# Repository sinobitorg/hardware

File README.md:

# sino:bit 八卦单机板

A single-board microcontroller for computer education in China<br>
专为中国电脑教育打造的一款微型单机板

The sino:bit is the first Chinese OSHWA Certified project:<br>
这块单机板是第一块中国真正被开源协会认证的项目<br>

### Quick Start
[Elecrow sells the sino:bit here.](https://www.elecrow.com/sino-bit-v1-0.html)

Adafruit has an [excellent tutorial written by David Astels](https://learn.adafruit.com/sino-bit-with-arduino/dastels-overview)

If you want to make an enclosure, [you can download CAD files of the board here.](https://a360.co/2mymH0g)

## Contents 内容
- [Introduction 介绍](#introduction-介绍)
  - [What it is 它是什么](#what-it-is-它是什么)
  - [Why it was created 创造原因](#why-it-was-created-创造原因)
  - [What it means 八卦单机板的意义](#what-it-means-八卦单机板的意义)
  - [Who are we 我们是谁](#who-are-we-我们是谁)
- [License 许可协议](#license-许可协议)

## Introduction 介绍

### What it is 它是什么

The sino:bit a single-board microcontroller designed for computer education in China. It is based on the [Calliope mini](https://calliope.cc) with permission of the [Calliope mini project](https://github.com/calliope-mini/).

While several modifications are planned, the first was to upgrade the LED matrix from 5x5 to 12x12. This allows for support of Chinese, Japanese, Hindi, Arabic and other non-Latin character based languages. Without this, the vast majority of the World's children cannot experience the thrill of that first "Hello World" in their own language.

八卦单机板是为中国打造的一款微型可编程计算机。是基于德国的 [Calliope mini](https://calliope.cc)获得官方准许后衍生出来的项目。在构思中国版本的时候有几个想法，其中一点就是把原有的5X5LED矩阵改为12X12。这样可支持多国语言，不仅只是英语，也可以显示中文，日本，印度语，阿拉伯语和其他不以拉丁语为基础的语言。如果保留原有的只是5X5矩阵，其他国家的孩子就无法体验到第一次显示屏弹出他们自己语言的“Hello, World”的那种激动兴奋的心情。

### Why it was created 创造原因

China has two issues to deal with in computer education. The first is the same as everyplace else in the world- the process of teaching coding and hardware fundamentals. The second is somewhat more unique to China and it's a problem we are known around the World for. How we copy. Children need to learn when we can copy, how we copy, and what our obligations are when we copy. Not out of any abstract moral obligation- but because copying and poor habits related to IP is standing in the way of China progressing economically.

If the quality and creativity of our engineering is going to improve, we need to begin teaching Open Source citizenship at a younger age. We cannot wait until engineers are graduating college to introduce them to the values of Open Source, by then habits are set and we have seen they are nearly impossible to change. This is a lesson that needs to be taught alongside other computing fundamentals from the time students are in primary school.

Our goal is that the sino:bit lineage- what it is derived from, what that means, and why Open Source is valuable; be taught from the beginning before a student writes their first line of code.

Original BBC micro:bits, in addition to not supporting Chinese language display, cannot compete on cost with locally made, license violating clones. Using these clones sets the worse possible example.

What China needs is an Open Source board priced appropriately for our level of economic development- cost-effective enough to supply one to every child as part of a nationally standardized curriculum, that is fully compliant with Open Source licenses and community standards.

在中国进行电脑教育面临着两大主要问题。第一个跟全世界一样的问题-利用更好的方法和途径去教育编程和硬件基础知识。第二个是相比较下针对中国的问题也因为如此被世界所闻，就是我们复制的方式。孩子需要有意识地知道我们应该什么时候复制，采用怎样的方式复制，还有了解作为复制者我们有着什么相应的义务。不是那种抽象的道德义务-而是因为我们完全复制的坏习惯与IP密切关联阻挡了中国发展的道路。

如果中国真心想提高工程师的质量和创造力，那么我们必须从娃娃抓起讲授开源并引导其成为一份子。要是等到工程师毕业以后才开始向他们介绍开源的核心价值观，那就为时已晚了，习惯一旦形成是很难被改变的。所以就应当把小学作为起点在教育电脑基础知识的同时教育他们开源的概念。

根据中华文化这块八卦板的最好的教育方式应该是从渊源入手-讲述它的来源，它的意义，它的开源价值；应该在学生写他们第一行代码前开始传授那些知识。

原始的BBC micro:bit不但无法显示中文，在价格上也无法本地制造商竞争，所以被山寨者在不遵守一定条例下肆意利用。使用这些山寨品来教育孩子是最坏的例子。

中国所需的开源教育开发板的价格应该以我们的经济发展水平作为参考-为了每个孩子都能够利用八卦单机板去学习而且被纳入所有学校课程教育的一部分，价格应该是合理划算的。

### What it means 八卦单机板的意义

Because much of technical education in China originates in the West, Chinese design and UI principles are usually absent.  Culturally the West favors black and grey, China is far more fond of red and gold. Time and text in the West go from left to right- traditionally in China it is top to bottom. 

With tech such a large part of our lives, and nearly all that tech Western in design and functionality, "modern" becomes synonymous with "Western" and we lose something of our history and culture. It's knives and forks instead of chopsticks, it's a latte in a mug instead of a red clay pot of Pu'er tea. All minor things, but it's a little bit of ourselves being chipped away every day. If the opportunity arises to reincorporate elements of our rich cultural tradition and offer it to children- it is essential to seize it.

The octagonal shape of the sino:bit is based on the Bagua- the eight trigrams used in Taoist cosmology and ancient Chinese philosophy. The Bagua is also an essential tool in Feng Shui and offers a chance for older family members to share this knowledge with young people- even collaborating with them to implement these traditions in electronic form.

The execution of characters, the art of calligraphy, the proper structure of poems and idioms- these are all aspects of education that receive far more emphasis in China than the West. The written word is such an essential part of Chinese education and culture, the loss in teaching without it cannot be underestimated, and the benefits to having hardware that supports its display cannot be overstated.<br>

因为目前在中国许多关于科学科技的教育取材于西方，相比下来中国的设计和UI都是凤毛麟角的。文化上西方偏向黑色和灰色，中国人更喜欢红色和金色。时间和文字在西方的顺序是从左到右罗列的，而在中国传统文化里面是由上到下排列。

科技已经成为我们生活不可分割的一部分了，几乎所有我们周围的电子科技设计和性能都是西方化的，“现代化”这个词就等同于“西方化”，我们丢失了自己的一部分历史还有文化。刀叉代替了筷子，装在马克杯里的拿铁代替了红色陶瓷杯里的普洱茶。这些看起来不起眼的事情，但却每天一点点的在侵蚀我们的生活。如果有机会把我们伟大的传统文化与现代科技相结合起来教育培养中国的孩子-我们应该及时抓住这个时机。

这块开发板就跟它的名字一样是根据我国八卦形状所设计的-八卦一直对道家的宇宙观和中国的传统哲学有着深远的影响。八卦是风水学中的重要工具，所以我们的八卦开发板有助于老一辈和其他年轻的家庭成员分享这个知识-即使需要把这个知识融入到电子产品以这个形式去达到目的。

使用文字传递信息。每个字在不同人的手下都有独特的形态和神韵，诗与成语-它们在中国的教育中比在西方教育中起到更加强大的作用。很多人往往忽视了文字文体在中国人眼中的重要性。如果不能使用现代教育工具去显示我们国家的文字，那些教育工具对于我们来说并非是举足轻重的。     
       
### Who are we 我们是谁

The sino:bit was created by [Naomi Wu](http://www.youtube.com/c/SexyCyborg), an Open Source Hardware evangelist and DIY enthusiast. It was executed and engineered by [Elecrow Technology](https://www.elecrow.com), a Shenzhen based electronics company that offers contract manufacturing and engineering services to Maker and Hardware Enthusiasts.

八卦单机板是由[Naomi Wu](http://www.youtube.com/c/SexyCyborg)所构思，一位开源硬件的传道者和DIY爱好者。由深圳本地为创客和硬件爱好者以合同形式提供代工业务的电子公司[Elecrow Technology](https://www.elecrow.com)所设计制作。

## License 许可协议

This software is licensed under the MIT License.
此软件请参考MIT软件许可协议

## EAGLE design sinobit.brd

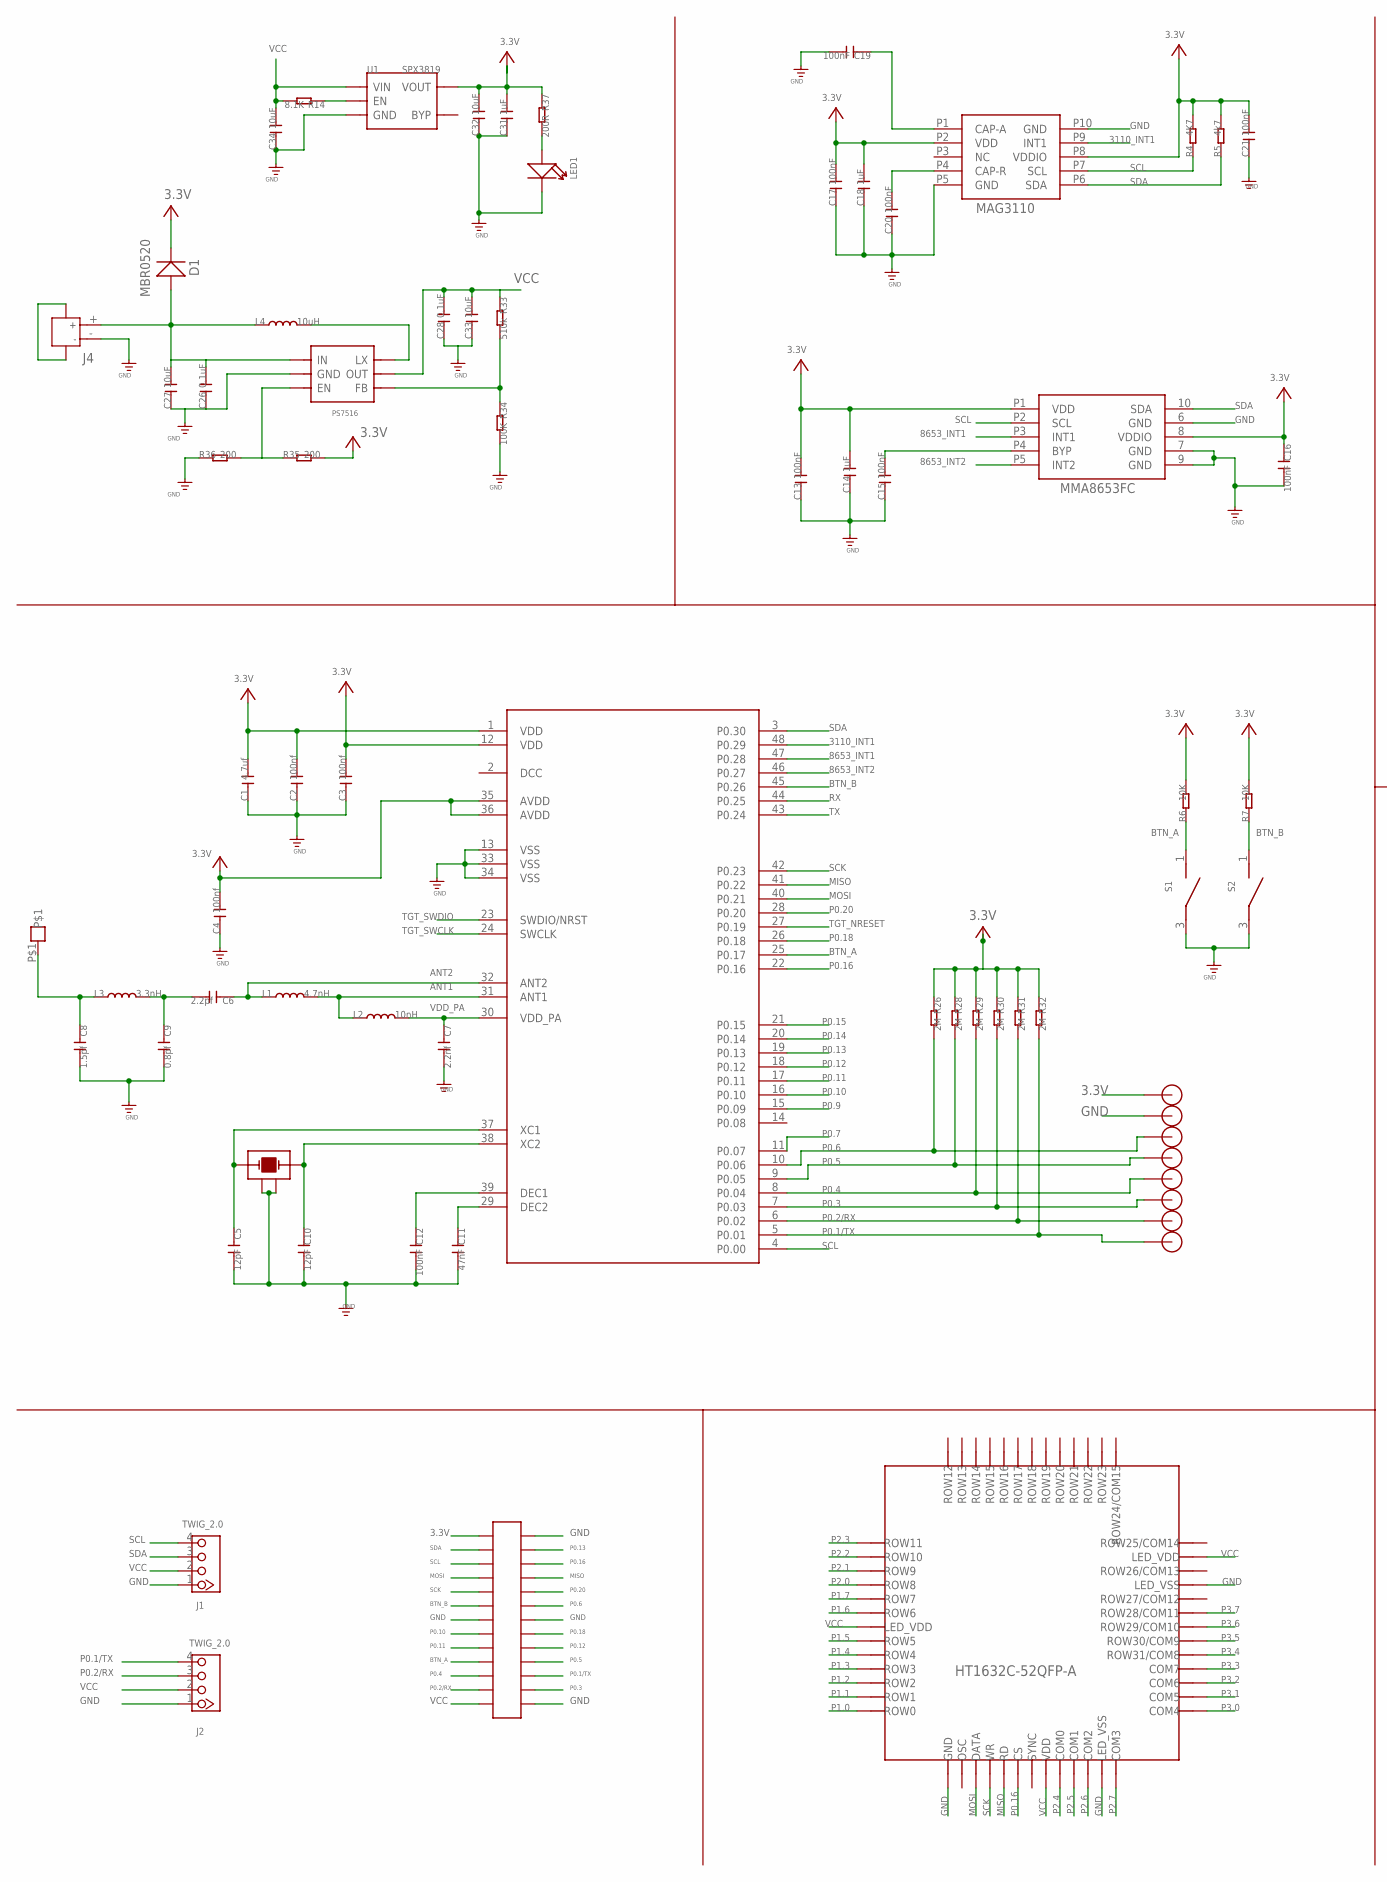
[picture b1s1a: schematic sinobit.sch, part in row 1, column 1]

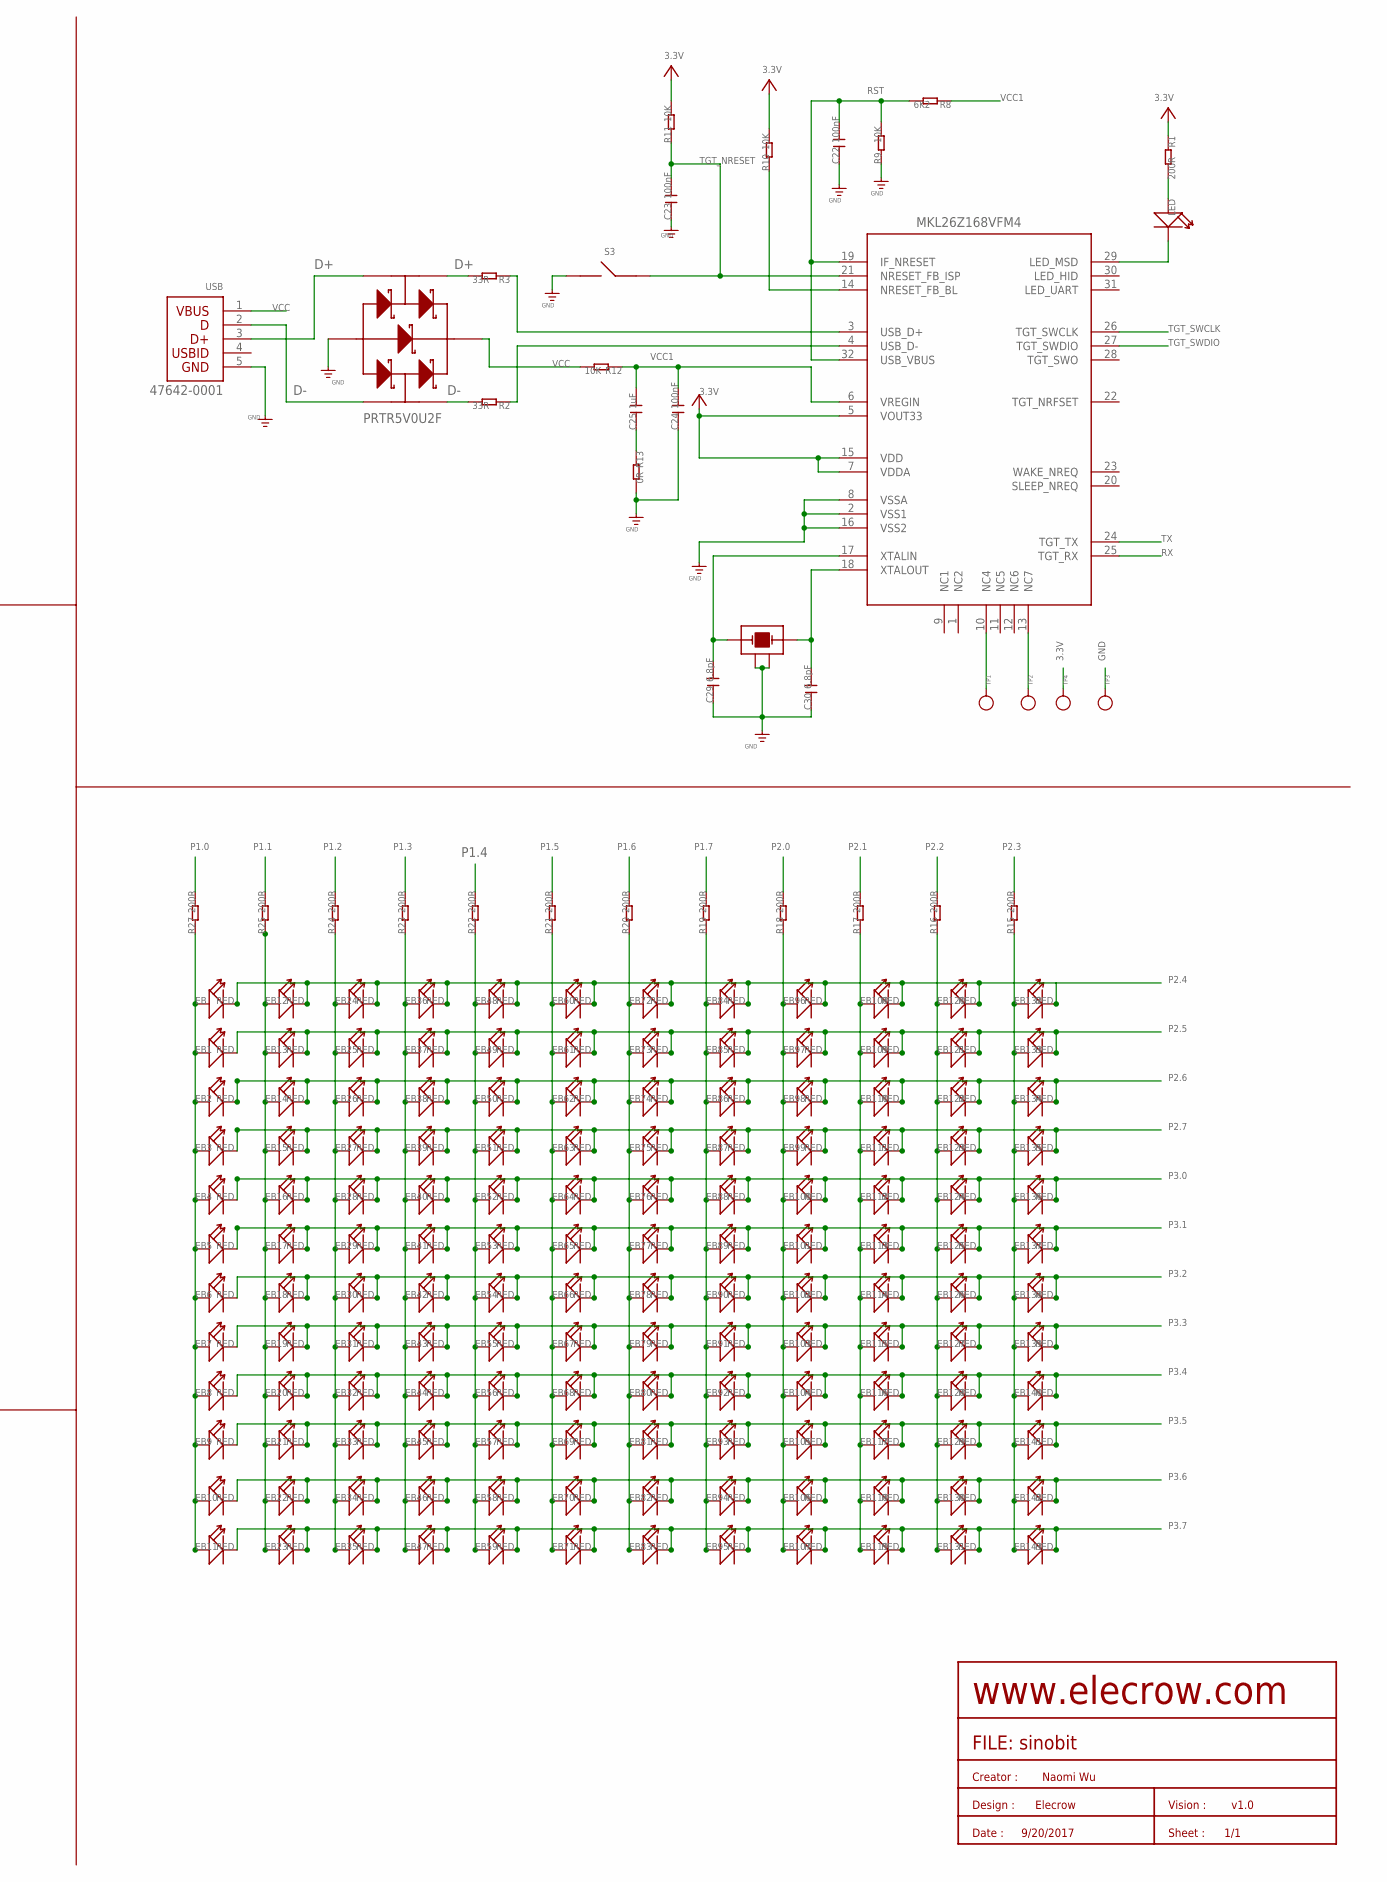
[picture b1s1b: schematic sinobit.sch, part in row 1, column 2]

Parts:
C1: 4.7uf; C0402
C2, C3, C4: 100nf; C0402
C5, C10: 12pF; C0402
C6: 2.2pf; C0402
C7: 2.2nf; C0402
C8: 1.5pf; C0402
C9: 0.8pf; C0402
C11: 47nF; C0402
C12, C13, C15, C16, C17, C19, C20, C21, C22, C23, C24: 100nF; C0402
C14, C18, C25, C31: 1uF; C0402
C26, C28: 0.1uF; C0402
C27, C32, C33, C34: 10uF; C0402
C29, C30: 6.8pF; C0402
D1: MBR0520; SOD123
EB, EB1, EB2, EB3, EB4, EB5, EB6, EB7, EB8, EB9, EB10, EB11, EB12, EB13, EB14, EB15, EB16, EB17, EB18, EB19, EB20, EB21, EB22, EB23, EB24, EB25, EB26, EB27, EB28, EB29, EB30, EB31, EB32, EB33, EB34, EB35, EB36, EB37, EB38, EB39, EB40, EB41, EB42, EB43, EB44, EB45, EB46, EB47, EB48, EB49, EB50, EB51, EB52, EB53, EB54, EB55, EB56, EB57, EB58, EB59, EB60, EB61, EB62, EB63, EB64, EB65, EB66, EB67, EB68, EB69, EB70, EB71, EB72, EB73, EB74, EB75, EB76, EB77, EB78, EB79, EB80, EB81, EB82, EB83, EB84, EB85, EB86, EB87, EB88, EB89, EB90, EB91, EB92, EB93, EB94, EB95, EB96, EB97, EB98, EB99, EB100, EB101, EB102, EB103, EB104, EB105, EB106, EB107, EB108, EB109, EB110, EB111, EB112, EB113, EB114, EB115, EB116, EB117, EB118, EB119, EB120, EB121, EB122, EB123, EB124, EB125, EB126, EB127, EB128, EB129, EB130, EB131, EB132, EB133, EB134, EB135, EB136, EB137, EB138, EB139, EB140, EB141, EB142, EB143: RED; D0603
J1, J2: TWIG_2.0; 2.0_1X4
J4: JACK-JST-2P-SMD-PW'2.0'; JST-SMD-2.0-90D
L1: 4.7nH; L0603
L2: 10nH; L0603
L3: 3.3nH; L0603
L4: 10uH; L0603
LED: blue; D0603
LED1: green; D0603
R1, R15, R16, R17, R18, R19, R20, R21, R22, R23, R24, R25, R27, R37: 200R; R0402
R2, R3: 33R; R0402
R4: 4K7; R0402
R5: 4k7; R0402
R6, R7, R9, R10, R11, R12: 10K; R0402
R8: 6K2; R0402
R13: 0R; R0402
R14: 8.1K; R0402
R26, R28, R29, R30, R31, R32: 2M; R0402
R33: 510k; R0402
R34: 100K; R0402
R35, R36: 200; R0402
S1, S2: SWITCH
S3: SWITCH4.5X4.5; SWITC4.5X4.5
TP1: PAD-TEST-POINT'4545'; TP_4545
TP2, TP3, TP4: PAD-TEST-POINT'4545'; TP_4545; PARTNO DNP
U1: SPX3819; SOT23-5
U2: IC_MAG3110FCR1; MAG3110
U3: D_ESD_PRTR5V0U2F_115; PRTR5V0U2F_SOT886
U6: IC_NRF51822_MODULE; NRF51822
U8: HT1632C_QFP52; HT1632C
U9, U10: 16MHZ2520
U11: TIANXIAN
U12: IC_MKL26Z128VFM4; MKL26Z168VFM4
U14: IC_MMA8653FCR1; MMA8653FC
U16: PS7516
U$12: 26PIN
U$35, U$39, U$46, U$48, U$49, U$50, U$51, U$52: 焊盘1
USB: 47642-0001

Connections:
3.3V: C1.2, C2.2, C3.2, C4.2, C13.2, C14.2, C16.1, C17.2, C18.2, C21.2, C31.2, C32.2, D1.-, R1.1, R4.2, R5.2, R6.2, R7.2, R10.2, R11.2, R26.1, R28.1, R29.1, R30.1, R31.1, R32.1, R35.2, R37.1, TP4.T, U1.5 (VOUT), U2.P2 (VDD), U2.P8 (VDDIO), U6.1 (VDD), U6.12 (VDD), U6.35 (AVDD), U6.36 (AVDD), U12.5 (VOUT33), U12.7 (VDDA), U12.15 (VDD), U14.8 (VDDIO), U14.P1 (VDD), U$12.P$13 (13), U$52.P$1
3110_INT1: U2.P9 (INT1), U6.48 (P0.29)
8653_INT1: U6.47 (P0.28), U14.P3 (INT1)
8653_INT2: U6.46 (P0.27), U14.P5 (INT2)
$1: EB.+, EB1.+, EB2.+, EB3.+, EB4.+, EB5.+, EB6.+, EB7.+, EB8.+, EB9.+, EB10.+, EB11.+, R27.1
$2: EB12.+, EB13.+, EB14.+, EB15.+, EB16.+, EB17.+, EB18.+, EB19.+, EB20.+, EB21.+, EB22.+, EB23.+, R25.1
$3: EB24.+, EB25.+, EB26.+, EB27.+, EB28.+, EB29.+, EB30.+, EB31.+, EB32.+, EB33.+, EB34.+, EB35.+, R24.1
$4: EB36.+, EB37.+, EB38.+, EB39.+, EB40.+, EB41.+, EB42.+, EB43.+, EB44.+, EB45.+, EB46.+, EB47.+, R23.1
$5: EB60.+, EB61.+, EB62.+, EB63.+, EB64.+, EB65.+, EB66.+, EB67.+, EB68.+, EB69.+, EB70.+, EB71.+, R21.1
$6: EB72.+, EB73.+, EB74.+, EB75.+, EB76.+, EB77.+, EB78.+, EB79.+, EB80.+, EB81.+, EB82.+, EB83.+, R20.1
$7: EB84.+, EB85.+, EB86.+, EB87.+, EB88.+, EB89.+, EB90.+, EB91.+, EB92.+, EB93.+, EB94.+, EB95.+, R19.1
$8: EB96.+, EB97.+, EB98.+, EB99.+, EB100.+, EB101.+, EB102.+, EB103.+, EB104.+, EB105.+, EB106.+, EB107.+, R18.1
$9: EB108.+, EB109.+, EB110.+, EB111.+, EB112.+, EB113.+, EB114.+, EB115.+, EB116.+, EB117.+, EB118.+, EB119.+, R17.1
$10: EB120.+, EB121.+, EB122.+, EB123.+, EB124.+, EB125.+, EB126.+, EB127.+, EB128.+, EB129.+, EB130.+, EB131.+, R16.1
$12: EB132.+, EB133.+, EB134.+, EB135.+, EB136.+, EB137.+, EB138.+, EB139.+, EB140.+, EB141.+, EB142.+, EB143.+, R15.1
$80: EB48.+, EB49.+, EB50.+, EB51.+, EB52.+, EB53.+, EB54.+, EB55.+, EB56.+, EB57.+, EB58.+, EB59.+, R22.1
ANT1: L1.2, L2.1, U6.31 (ANT1)
ANT2: C6.1, L1.1, U6.32 (ANT2)
BTN_A: R6.1, S1.1, U6.25 (P0.17), U$12.P$4 (4)
BTN_B: R7.1, S2.1, U6.45 (P0.26), U$12.P$8 (8)
D+: R3.2, U3.P3 (3), U3.P4 (4), USB.3
D-: R2.2, U3.P1 (1), U3.P6 (6), USB.2
GND: C1.1, C2.1, C3.1, C4.1, C5.2, C7.2, C8.2, C9.2, C10.2, C11.2, C12.2, C13.1, C14.1, C15.1, C16.2, C17.1, C18.1, C19.2, C20.1, C21.1, C22.1, C23.1, C24.1, C26.1, C27.1, C28.1, C29.1, C30.1, C31.1, C32.1, C33.1, C34.1, J1.1, J2.1, J4.- (2), LED1.-, R9.1, R13.2, R34.2, R36.1, S1.3, S2.3, S3.P$1, TP3.T, U1.2 (GND), U2.P5 (GND), U2.P10 (GND), U3.P2 (2), U6.13 (VSS), U6.33 (VSS), U6.34 (VSS), U8.P$8 (GND), U8.P$19 (LED_VSS), U8.P$30 (LED_VSS), U9.2, U9.4, U10.2, U10.4, U12.2 (VSS1), U12.8 (VSSA), U12.16 (VSS2), U14.6 (GND), U14.7 (GND), U14.9 (GND), U16.P2 (GND), U$12.P$7 (7), U$12.P$14 (14), U$12.P$20 (20), U$12.P$26 (26), U$46.P$1, USB.5
MISO: U6.41 (P0.22), U8.P$12 (RD), U$12.P$17 (17)
MOSI: U6.40 (P0.21), U8.P$10 (DATA), U$12.P$10 (10)
unnamed: C20.2, U2.P4 (CAP-R)
unnamed: C19.1, U2.P1 (CAP-A)
unnamed: R10.1, U12.14 (NRESET_FB_BL)
unnamed: C15.2, U14.P4 (BYP)
unnamed: LED1.+, R37.2
unnamed: LED.+, R1.2
unnamed: TP1.T, U12.10 (NC4)
unnamed: TP2.T, U12.13 (NC7)
unnamed: LED.-, U12.29 (LED_MSD)
unnamed: C25.1, R13.1
unnamed: J4.3, J4.4
unnamed: R3.1, U12.3 (USB_D+)
unnamed: R2.1, U12.4 (USB_D-)
unnamed: C29.2, U10.1, U12.17 (XTALIN)
unnamed: C30.2, U10.3, U12.18 (XTALOUT)
unnamed: R35.1, R36.2, U16.P4 (EN)
unnamed: C26.2, C27.2, D1.+, J4.+ (1), L4.1, U16.P6 (IN)
unnamed: C6.2, C9.1, L3.2
unnamed: R14.1, U1.3 (EN)
unnamed: L4.2, U16.P1 (LX)
unnamed: C8.1, L3.1, U11.P$1
unnamed: C5.1, U6.37 (XC1), U9.1
unnamed: R33.2, R34.1, U16.P3 (FB)
unnamed: C10.1, U6.38 (XC2), U9.3
unnamed: C11.1, U6.29 (DEC2)
unnamed: C12.1, U6.39 (DEC1)
P0.1/TX: J2.4, R32.2, U6.5 (P0.01), U$12.P$24 (24), U$39.P$1
P0.2/RX: J2.3, R31.2, U6.6 (P0.02), U$12.P$2 (2), U$35.P$1
P0.3: R30.2, U6.7 (P0.03), U$12.P$25 (25), U$51.P$1
P0.4: R29.2, U6.8 (P0.04), U$12.P$3 (3), U$50.P$1
P0.5: R28.2, U6.9 (P0.05), U$12.P$23 (23), U$49.P$1
P0.6: R26.2, U6.10 (P0.06), U$12.P$19 (19), U$48.P$1
P0.7: U6.11 (P0.07)
P0.9: U6.15 (P0.09)
P0.10: U6.16 (P0.10), U$12.P$6 (6)
P0.11: U6.17 (P0.11), U$12.P$5 (5)
P0.12: U6.18 (P0.12), U$12.P$22 (22)
P0.13: U6.19 (P0.13), U$12.P$15 (15)
P0.14: U6.20 (P0.14)
P0.15: U6.21 (P0.15)
P0.16: U6.22 (P0.16), U8.P$13 (CS), U$12.P$16 (16)
P0.18: U6.26 (P0.18), U$12.P$21 (21)
P0.20: U6.28 (P0.20), U$12.P$18 (18)
P1.0: R27.2, U8.P$47 (ROW0)
P1.1: R25.2, U8.P$48 (ROW1)
P1.2: R24.2, U8.P$49 (ROW2)
P1.3: R23.2, U8.P$50 (ROW3)
P1.4: R22.2, U8.P$51 (ROW4)
P1.5: R21.2, U8.P$52 (ROW5)
P1.6: R20.2, U8.P$54 (ROW6)
P1.7: R19.2, U8.P$55 (ROW7)
P2.0: R18.2, U8.P$56 (ROW8)
P2.1: R17.2, U8.P$57 (ROW9)
P2.2: R16.2, U8.P$58 (ROW10)
P2.3: R15.2, U8.P$59 (ROW11)
P2.4: EB.-, EB12.-, EB24.-, EB36.-, EB48.-, EB60.-, EB72.-, EB84.-, EB96.-, EB108.-, EB120.-, EB132.-, U8.P$16 (COM0)
P2.5: EB1.-, EB13.-, EB25.-, EB37.-, EB49.-, EB61.-, EB73.-, EB85.-, EB97.-, EB109.-, EB121.-, EB133.-, U8.P$17 (COM1)
P2.6: EB2.-, EB14.-, EB26.-, EB38.-, EB50.-, EB62.-, EB74.-, EB86.-, EB98.-, EB110.-, EB122.-, EB134.-, U8.P$18 (COM2)
P2.7: EB3.-, EB15.-, EB27.-, EB39.-, EB51.-, EB63.-, EB75.-, EB87.-, EB99.-, EB111.-, EB123.-, EB135.-, U8.P$20 (COM3)
P3.0: EB4.-, EB16.-, EB28.-, EB40.-, EB52.-, EB64.-, EB76.-, EB88.-, EB100.-, EB112.-, EB124.-, EB136.-, U8.P$21 (COM4)
P3.1: EB5.-, EB17.-, EB29.-, EB41.-, EB53.-, EB65.-, EB77.-, EB89.-, EB101.-, EB113.-, EB125.-, EB137.-, U8.P$22 (COM5)
P3.2: EB6.-, EB18.-, EB30.-, EB42.-, EB54.-, EB66.-, EB78.-, EB90.-, EB102.-, EB114.-, EB126.-, EB138.-, U8.P$23 (COM6)
P3.3: EB7.-, EB19.-, EB31.-, EB43.-, EB55.-, EB67.-, EB79.-, EB91.-, EB103.-, EB115.-, EB127.-, EB139.-, U8.P$24 (COM7)
P3.4: EB8.-, EB20.-, EB32.-, EB44.-, EB56.-, EB68.-, EB80.-, EB92.-, EB104.-, EB116.-, EB128.-, EB140.-, U8.P$25 (ROW31/COM8)
P3.5: EB9.-, EB21.-, EB33.-, EB45.-, EB57.-, EB69.-, EB81.-, EB93.-, EB105.-, EB117.-, EB129.-, EB141.-, U8.P$26 (ROW30/COM9)
P3.6: EB10.-, EB22.-, EB34.-, EB46.-, EB58.-, EB70.-, EB82.-, EB94.-, EB106.-, EB118.-, EB130.-, EB142.-, U8.P$27 (ROW29/COM10)
P3.7: EB11.-, EB23.-, EB35.-, EB47.-, EB59.-, EB71.-, EB83.-, EB95.-, EB107.-, EB119.-, EB131.-, EB143.-, U8.P$28 (ROW28/COM11)
RST: C22.2, R8.2, R9.2, U12.19 (IF_NRESET), U12.32 (USB_VBUS)
RX: U6.44 (P0.25), U12.25 (TGT_RX)
SCK: U6.42 (P0.23), U8.P$11 (WR), U$12.P$9 (9)
SCL: J1.4, R4.1, U2.P7 (SCL), U6.4 (P0.00), U14.P2 (SCL), U$12.P$11 (11)
SDA: J1.3, R5.1, U2.P6 (SDA), U6.3 (P0.30), U14.10 (SDA), U$12.P$12 (12)
TGT_NRESET: C23.2, R11.1, S3.P$2, U6.27 (P0.19), U12.21 (NRESET_FB_ISP)
TGT_SWCLK: U6.24 (SWCLK), U12.26 (TGT_SWCLK)
TGT_SWDIO: U6.23 (SWDIO/NRST), U12.27 (TGT_SWDIO)
TX: U6.43 (P0.24), U12.24 (TGT_TX)
VCC: C28.2, C33.2, C34.2, J1.2, J2.2, R12.2, R14.2, R33.1, U1.1 (VIN), U3.P5 (5), U8.P$15 (VDD), U8.P$32 (LED_VDD), U8.P$53 (LED_VDD), U16.P5 (OUT), U$12.P$1 (1), USB.1
VCC1: C24.2, C25.2, R8.1, R12.1, U12.6 (VREGIN)
VDD_PA: C7.1, L2.2, U6.30 (VDD_PA)

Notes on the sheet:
www.elecrow.com
FILE: sinobit
Design :
Sheet :
Date :
Vision :
Elecrow
v1.0
9/20/2017
1/1
Creator :
Naomi Wu

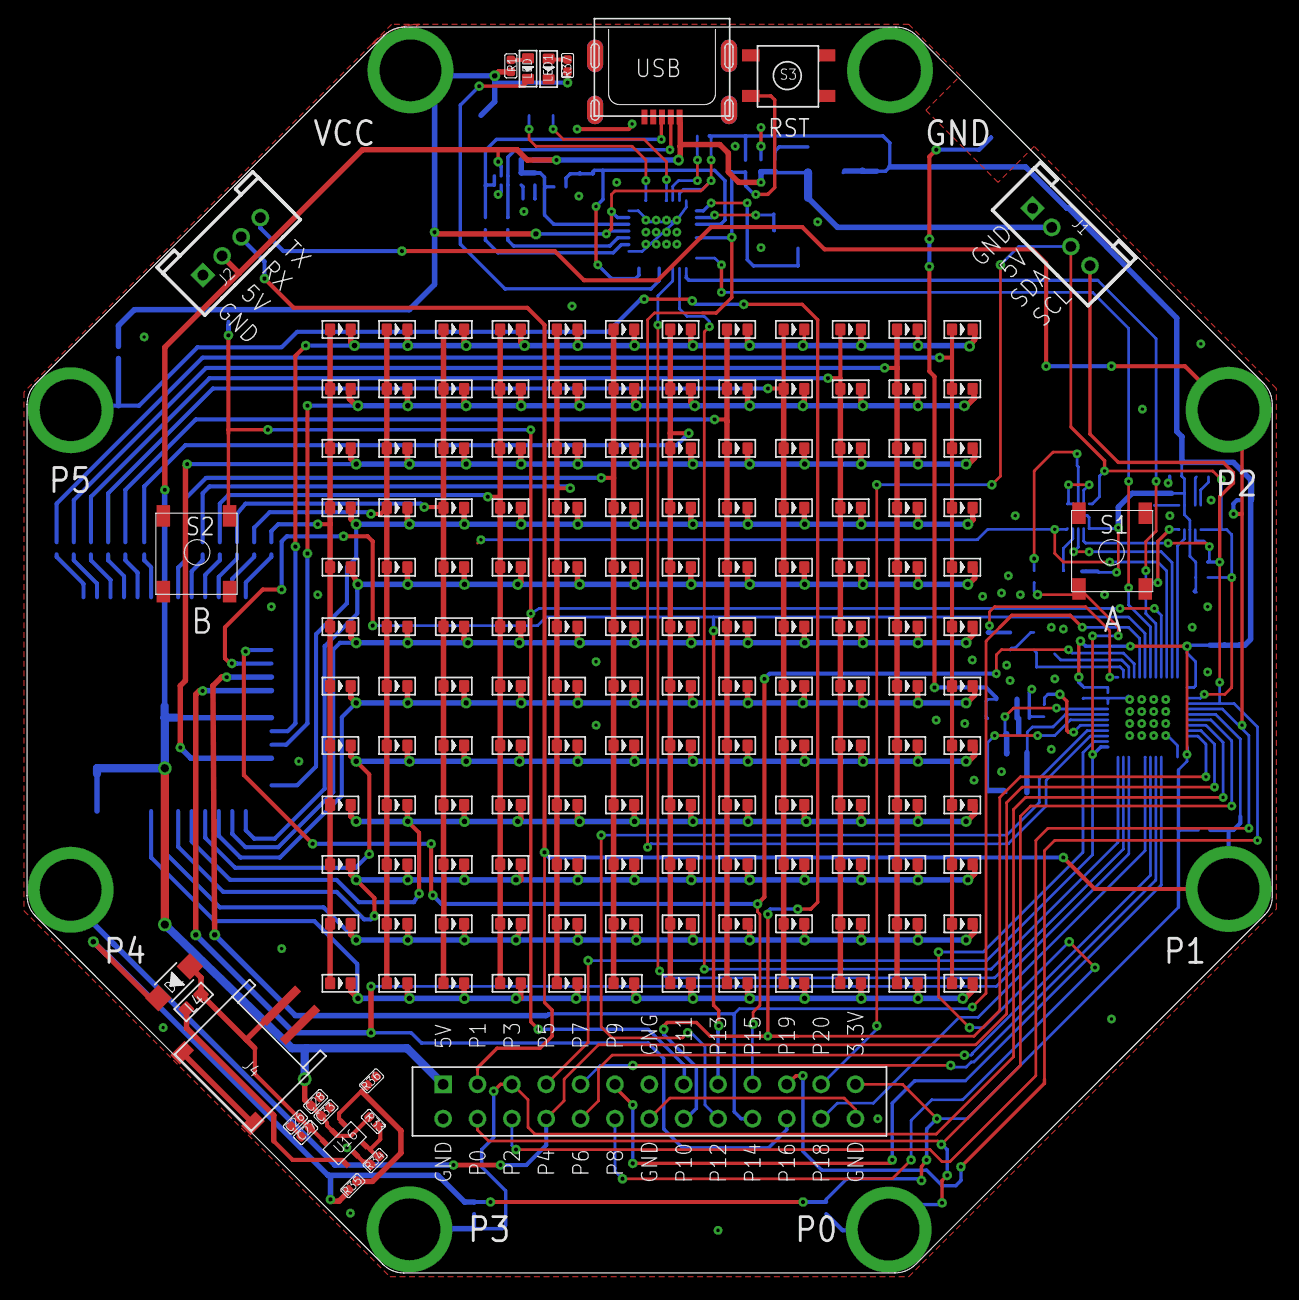
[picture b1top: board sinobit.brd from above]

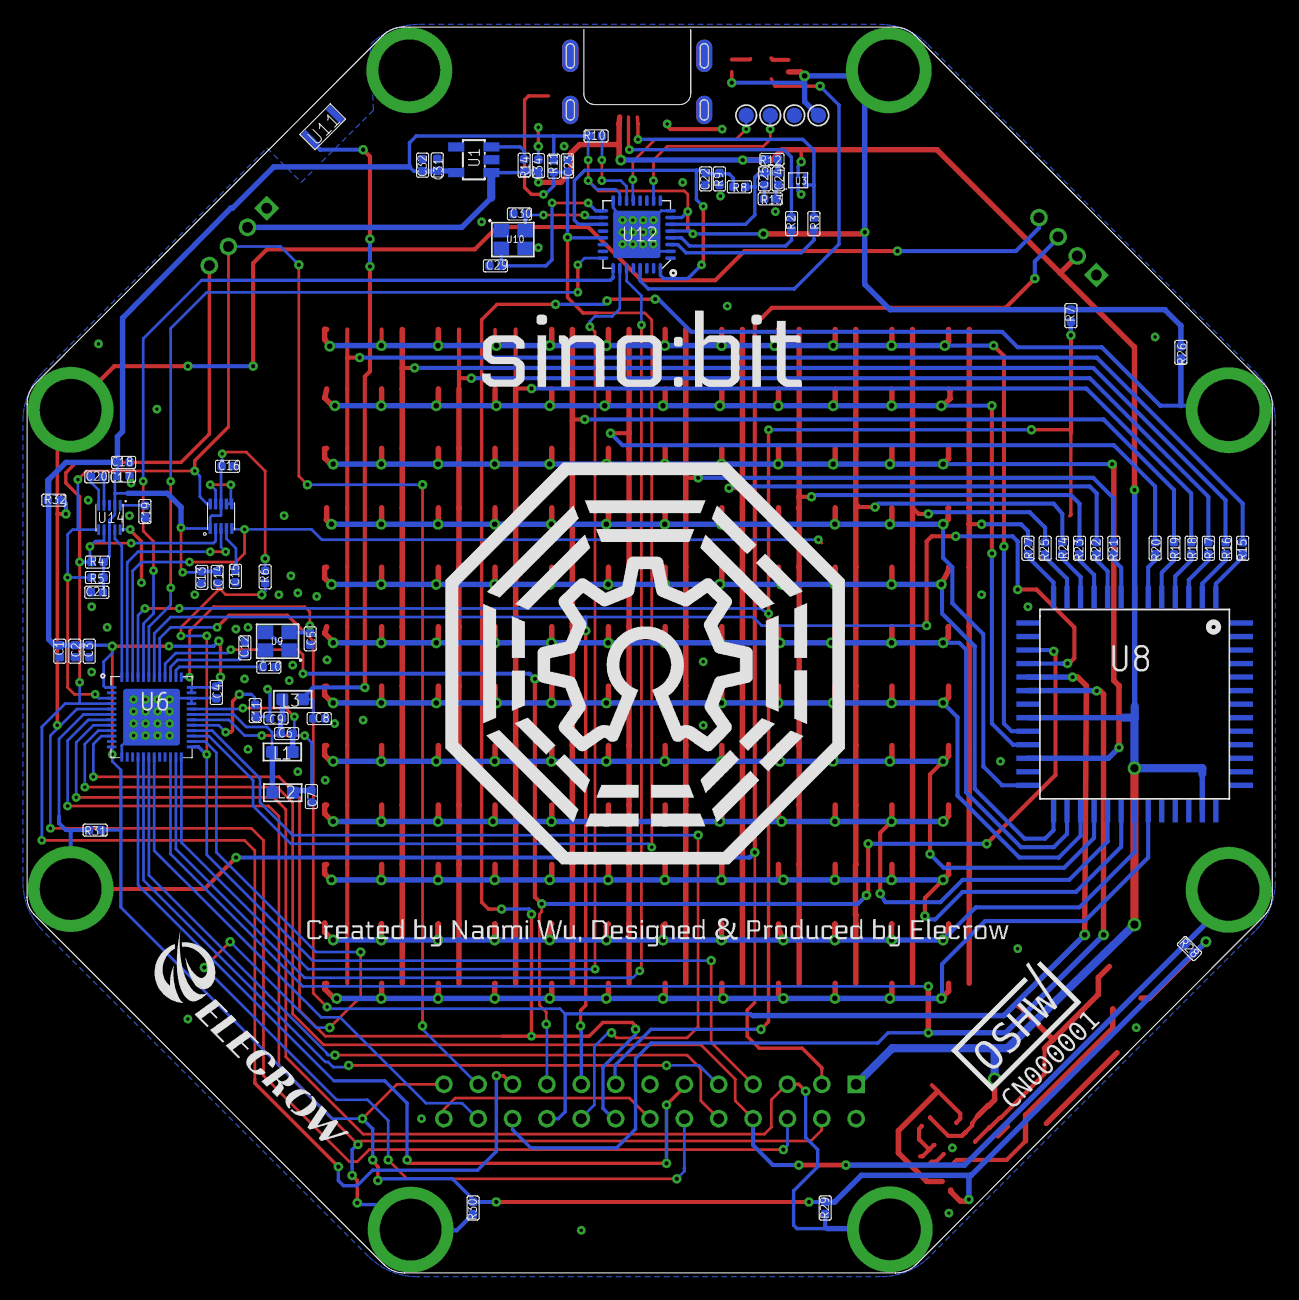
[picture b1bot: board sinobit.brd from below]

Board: 2 copper layers, 92.0 x 92.1 mm, 258 parts (91 on the bottom side), 100 nets.

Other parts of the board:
E$1: 文字
E$2: SINOBIT2
E$3: ELECEOW
E$4: SINOBIT编号
E$5: XXX

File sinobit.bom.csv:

"Qty";"Value";"Device";"Package";"Parts";"Description";"PARTNO";
"1";"";"D_ESD_PRTR5V0U2F_115";"PRTR5V0U2F_SOT886";"U3";"";"";
"1";"";"IC_MAG3110FCR1";"MAG3110";"U2";"";"";
"1";"";"JACK-JST-2P-SMD-PW'2.0'";"JST-SMD-2.0-90D";"J4";"";"";
"4";"";"PAD-TEST-POINT'4545'";"TP_4545";"TP1, TP2, TP3, TP4";"";"DNP";
"2";"0.1uF";"C-0402";"C0402";"C26, C28";"Ceramic Capacitors";"";
"1";"0.8pf";"C-0402";"C0402";"C9";"Ceramic Capacitors";"";
"1";"0R";"R-0402";"R0402";"R13";"";"";
"1";"1.5pf";"C-0402";"C0402";"C8";"Ceramic Capacitors";"";
"1";"100K";"R-0402";"R0402";"R34";"";"";
"11";"100nF";"C-0402";"C0402";"C12, C13, C15, C16, C17, C19, C20, C21, C22, C23, C24";"Ceramic Capacitors";"";
"3";"100nf";"C-0402";"C0402";"C2, C3, C4";"Ceramic Capacitors";"";
"6";"10K";"R-0402";"R0402";"R6, R7, R9, R10, R11, R12";"";"";
"1";"10nH";"L-0603";"L0603";"L2";"";"";
"3";"10uF";"C-0402";"C0402";"C27, C32, C34";"Ceramic Capacitors";"";
"1";"10uH";"L-0603";"L0603";"L4";"";"";
"2";"12pF";"C-0402";"C0402";"C5, C10";"Ceramic Capacitors";"";
"2";"16MHZ2520";"16MHZ2520";"16MHZ2520";"U9, U10";"";"";
"4";"1uF";"C-0402";"C0402";"C14, C18, C25, C31";"Ceramic Capacitors";"";
"1";"2.2nf";"C-0402";"C0402";"C7";"Ceramic Capacitors";"";
"1";"2.2pf";"C-0402";"C0402";"C6";"Ceramic Capacitors";"";
"2";"200";"R-0402";"R0402";"R35, R36";"";"";
"14";"200R";"R-0402";"R0402";"R1, R15, R16, R17, R18, R19, R20, R21, R22, R23, R24, R25, R27, R37";"";"";
"1";"22uF";"C-0402";"C0402";"C33";"Ceramic Capacitors";"";
"1";"26PIN";"26PIN";"26PIN";"U$12";"";"";
"6";"3.3M";"R-0402";"R0402";"R26, R28, R29, R30, R31, R32";"";"";
"1";"3.3nH";"L-0603";"L0603";"L3";"";"";
"2";"33R";"R-0402";"R0402";"R2, R3";"";"";
"1";"4.7nH";"L-0603";"L0603";"L1";"";"";
"1";"4.7uf";"C-0402";"C0402";"C1";"Ceramic Capacitors";"";
"1";"47642-0001";"47642-0001";"47642-0001";"USB";"";"";
"1";"47nF";"C-0402";"C0402";"C11";"Ceramic Capacitors";"";
"1";"4K7";"R-0402";"R0402";"R4";"";"";
"1";"4k7";"R-0402";"R0402";"R5";"";"";
"1";"525K";"R-0402";"R0402";"R33";"";"";
"2";"6.8pF";"C-0402";"C0402";"C29, C30";"Ceramic Capacitors";"";
"1";"6K2";"R-0402";"R0402";"R8";"";"";
"1";"8.1K";"R-0402";"R0402";"R14";"";"";
"1";"HT1632C_QFP52";"HT1632C_QFP52";"HT1632C";"U8";"";"";
"1";"IC_MKL26Z128VFM4";"IC_MKL26Z128VFM4";"MKL26Z168VFM4";"U$7";"";"";
"1";"IC_MMA8653FCR1";"IC_MMA8653FCR1";"MMA8653FC";"U$13";"";"";
"1";"IC_NRF51822_MODULE";"IC_NRF51822_MODULE";"NRF51822";"U6";"";"";
"1";"MBR0520";"D'1206'";"SOD123";"D1";"";"";
"1";"PS7516";"PS7516";"PS7516";"U$4";"";"";
"144";"RED";"007-LED0603";"D0603";"EB, EB1, EB2, EB3, EB4, EB5, EB6, EB7, EB8, EB9, EB10, EB11, EB12, EB13, EB14, EB15, EB16, EB17, EB18, EB19, EB20, EB21, EB22, EB23, EB24, EB25, EB26, EB27, EB28, EB29, EB30, EB31, EB32, EB33, EB34, EB35, EB36, EB37, EB38, EB39, EB40, EB41, EB42, EB43, EB44, EB45, EB46, EB47, EB48, EB49, EB50, EB51, EB52, EB53, EB54, EB55, EB56, EB57, EB58, EB59, EB60, EB61, EB62, EB63, EB64, EB65, EB66, EB67, EB68, EB69, EB70, EB71, EB72, EB73, EB74, EB75, EB76, EB77, EB78, EB79, EB80, EB81, EB82, EB83, EB84, EB85, EB86, EB87, EB88, EB89, EB90, EB91, EB92, EB93, EB94, EB95, EB96, EB97, EB98, EB99, EB100, EB101, EB102, EB103, EB104, EB105, EB106, EB107, EB108, EB109, EB110, EB111, EB112, EB113, EB114, EB115, EB116, EB117, EB118, EB119, EB120, EB121, EB122, EB123, EB124, EB125, EB126, EB127, EB128, EB129, EB130, EB131, EB132, EB133, EB134, EB135, EB136, EB137, EB138, EB139, EB140, EB141, EB142, EB143";"";"";
"1";"SPX3819";"SPX3819";"SOT23-5";"U1";"";"";
"2";"SWITCH";"SWITCH";"SWITCH";"S1, S2";"";"";
"1";"SWITCH4.5X4.5";"SWITCH4.5X4.5";"SWITC4.5X4.5";"S3";"";"";
"1";"TIANXIAN";"TIANXIAN";"TIANXIAN";"U$6";"";"";
"2";"TWIG_2.0";"TWIG_2.0";"2.0_1X4";"J1, J2";"";"";
"1";"blue";"007-LED0603";"D0603";"LED";"";"";
"1";"green";"007-LED0603";"D0603";"LED1";"";"";
"8";"焊盘1";"焊盘1";"焊盘1";"U$35, U$39, U$46, U$48, U$49, U$50, U$51, U$52";"";"";

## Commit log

2017-10-13 sinobit
2017-11-05 Bills of Materials in CSV, HTML, and TXT formats
2017-11-06 sinobit-V1.0
2017-11-09 Add:image_drawing.html
2017-11-29 Create LICENSE
2017-12-06 fixing internal markdown links
2018-03-03 LED-Matrix.cpp : make HT1632C_Write_DAT() preserve its input data array HT1632C_Write_DAT(unsigned char Addr,const unsigned char data[],unsigned char num)
2018-03-03 image_draw.html : allow up to 32 bits per word
